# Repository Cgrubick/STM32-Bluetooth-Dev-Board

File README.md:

# STM32-Bluetooth-Dev-Board
STM32 based PCB design
By Clayton Grubick

Overview

This repository contains the design files, firmware, and documentation for a custom-designed PCB featuring an STM32 microcontroller with Bluetooth capabilities. The project is aimed at demonstrating advanced PCB design techniques, including RF circuitry for Bluetooth communication, making it suitable for a wide range of wireless applications.

Features:

  -STM32WB55CEU6 : Utilizes a high-performance STM32 MCU, offering ample processing power for complex applications

  -USB-C Connectivity: Utlizied USB-C with USB2.0 for connecting to the board and communication and power supply. Paired with the USB ESD protection IC

  -LDO Regulator: 5V to 3.3V supply

  -SWD Intereface: SWD connection for programming and debugging

  -RF Circuit: Impedence matching network and a LPF directed into a coaxial connection

  -Bootloader Button: Debouncing circuit and bootloader switch for firmware

  -UART Header Connection

This was my first higher level PCB design and also my first try at designing RF circuits, while the RF portion in this board is pretty trivial it was still a great exercise.

The low pass filter footprint is custom and the 3D model is also included under the 3D models folder, more info and data sheets are also included.

Schematic

PCB

3D view

TODO:

  -Manafuacture PCB
  
  -Write and load firmware onto board
  
  -Perform some simple embedded project with the board such as communication over bluetooth and sending and recieving data from an external computer

Credit/Inspo: Phils Lab

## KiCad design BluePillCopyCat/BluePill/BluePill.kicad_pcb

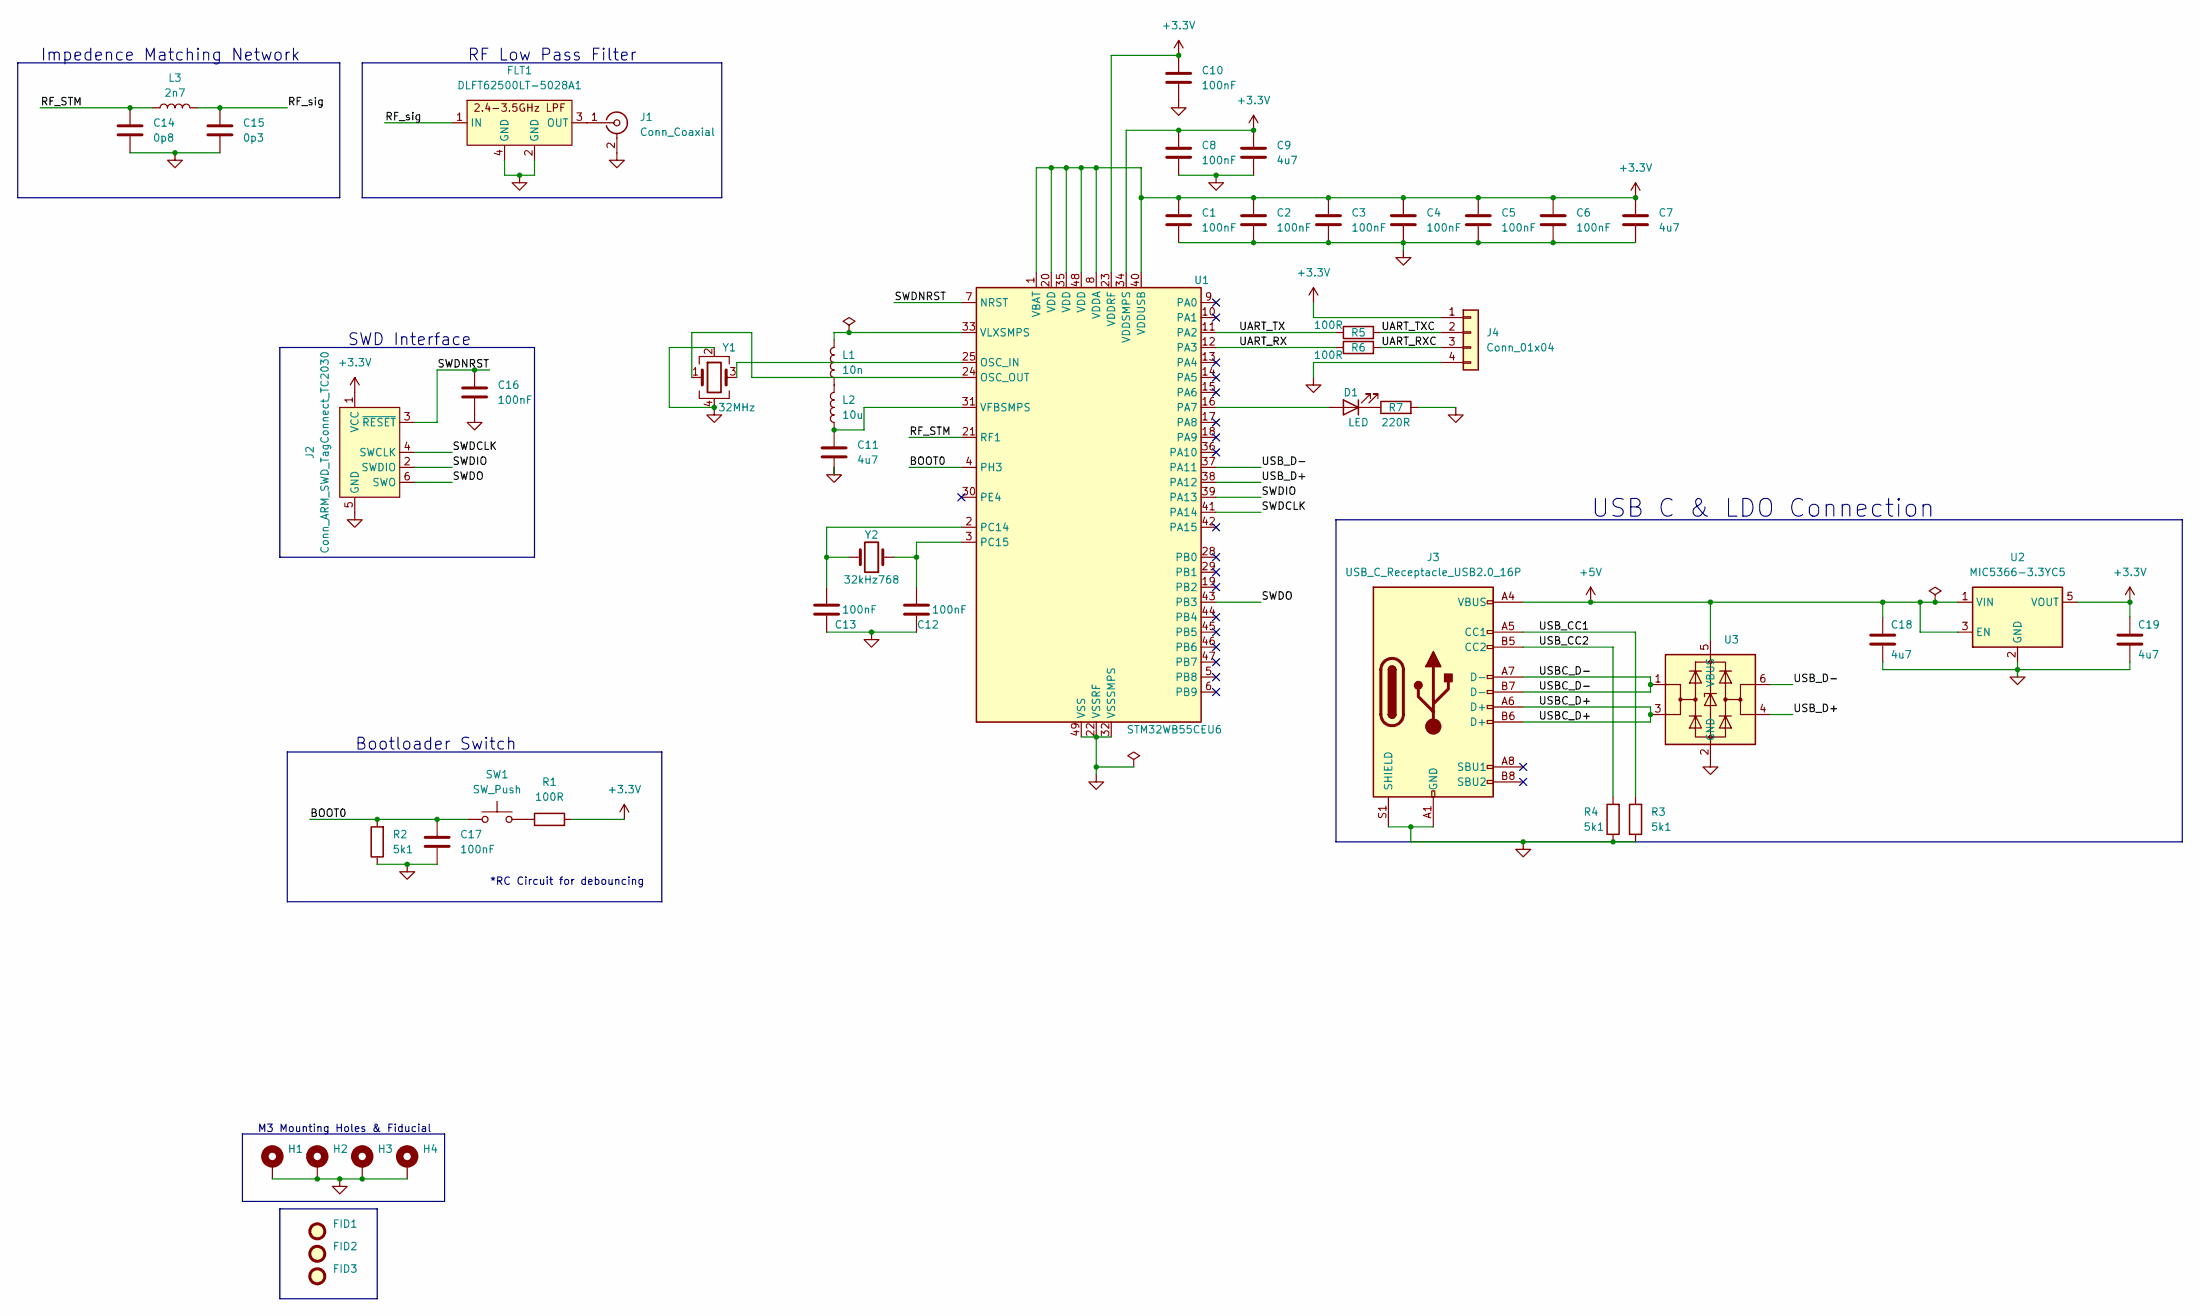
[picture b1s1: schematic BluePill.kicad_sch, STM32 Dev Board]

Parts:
C1, C2, C3, C4, C5, C6, C8, C10, C12, C13, C16, C17: 100nF; C_0402_1005Metric
C7, C9, C11, C18, C19: 4u7; C_0603_1608Metric
C14: 0p8; C_0402_1005Metric
C15: 0p3; C_0402_1005Metric
D1: LED; LED_0402_1005Metric
FID1, FID2, FID3: Fiducial; Fiducial_1mm_Mask2mm
FLT1: DLFT62500LT-5028A1
H1, H2, H3, H4: MountingHole_Pad; MountingHole_2.2mm_M2_Pad_Via
J1: Conn_Coaxial; U.FL_Hirose_U.FL-R-SMT-1_Vertical
J2: Conn_ARM_SWD_TagConnect_TC2030; Tag-Connect_TC2030-IDC-FP_2x03_P1.27mm_Vertical
J3: USB_C_Receptacle_USB2.0_16P; USB_C_Receptacle_GCT_USB4105-xx-A_16P_TopMnt_Horizontal
J4: Conn_01x04; PinSocket_1x04_P2.54mm_Vertical
L1: 10n; L_0402_1005Metric
L2: 10u; L_0805_2012Metric
L3: 2n7; L_0402_1005Metric
R1, R5, R6: 100R; R_0402_1005Metric
R2, R3, R4: 5k1; R_0402_1005Metric
R7: 220R; R_0402_1005Metric
SW1: SW_Push; SW_SPST_CK_RS282G05A3
U1: STM32WB55CEU6; QFN-48-1EP_7x7mm_P0.5mm_EP5.6x5.6mm
U2: MIC5366-3.3YC5; SOT-23-5
U3: SOT-23-6
Y1: 32MHz; Crystal_SMD_2016-4Pin_2.0x1.6mm
Y2: 32kHz768; Crystal_SMD_2012-2Pin_2.0x1.2mm

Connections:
+3.3V: C1.1, C2.1, C3.1, C4.1, C5.1, C6.1, C7.1, C8.1, C9.1, C10.1, C19.1, J2.1 (VCC), J4.1, R1.2, U1.1 (VBAT), U1.8 (VDDA), U1.20 (VDD), U1.23 (VDDRF), U1.34 (VDDSMPS), U1.35 (VDD), U1.40 (VDDUSB), U1.48 (VDD), U2.5 (VOUT)
+5V: C18.1, J3.A4 (VBUS), J3.A9 (VBUS), J3.B4 (VBUS), J3.B9 (VBUS), U2.1 (VIN), U2.3 (EN), U3.5 (VBUS)
/BOOT0: C17.1, R2.2, SW1.1, U1.4 (PH3)
/RF_STM: C14.1, L3.1, U1.21 (RF1)
/RF_sig: C15.1, FLT1.1 (IN), L3.2
/SWDCLK: J2.4 (SWCLK), U1.41 (PA14)
/SWDIO: J2.2 (SWDIO), U1.39 (PA13)
/SWDNRST: C16.1, J2.3 (~RESET), U1.7 (NRST)
/SWDO: J2.6 (SWO), U1.43 (PB3)
/UART_RX: R6.1, U1.12 (PA3)
/UART_RXC: J4.3, R6.2
/UART_TX: R5.1, U1.11 (PA2)
/UART_TXC: J4.2, R5.2
/USBC_D+: J3.A6 (D+), J3.B6 (D+), U3.3
/USBC_D-: J3.A7 (D-), J3.B7 (D-), U3.1
/USB_CC1: J3.A5 (CC1), R3.2
/USB_CC2: J3.B5 (CC2), R4.2
/USB_D+: U1.38 (PA12), U3.4
/USB_D-: U1.37 (PA11), U3.6
GND: C1.2, C2.2, C3.2, C4.2, C5.2, C6.2, C7.2, C8.2, C9.2, C10.2, C11.2, C12.1, C13.1, C14.2, C15.2, C16.2, C17.2, C18.2, C19.2, FLT1.2 (GND), FLT1.4 (GND), H1.1, H2.1, H3.1, H4.1, J1.2 (Ext), J2.5 (GND), J3.A1 (GND), J3.A12 (GND), J3.B1 (GND), J3.B12 (GND), J3.S1 (SHIELD), J4.4, R2.1, R3.1, R4.1, R7.2, U1.22 (VSSRF), U1.32 (VSSSMPS), U1.49 (VSS), U2.2 (GND), U3.2 (GND), Y1.2, Y1.4
unnamed: D1.2 (A), U1.16 (PA7)
unnamed: D1.1 (K), R7.1
unnamed: FLT1.3 (OUT), J1.1 (In)
unnamed: L1.1, L2.2
unnamed: R1.1, SW1.2
unnamed: U1.25 (OSC_IN), Y1.3
unnamed: U1.24 (OSC_OUT), Y1.1
unnamed: C13.2, U1.2 (PC14), Y2.2
unnamed: C12.2, U1.3 (PC15), Y2.1
unnamed: C11.1, L2.1, U1.31 (VFBSMPS)
unnamed: L1.2, U1.33 (VLXSMPS)

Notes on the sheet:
SWD Interface
M3 Mounting Holes & Fiducial
*RC Circuit for debouncing
RF Low Pass Filter
USB C & LDO Connection
Bootloader Switch
Impedence Matching Network

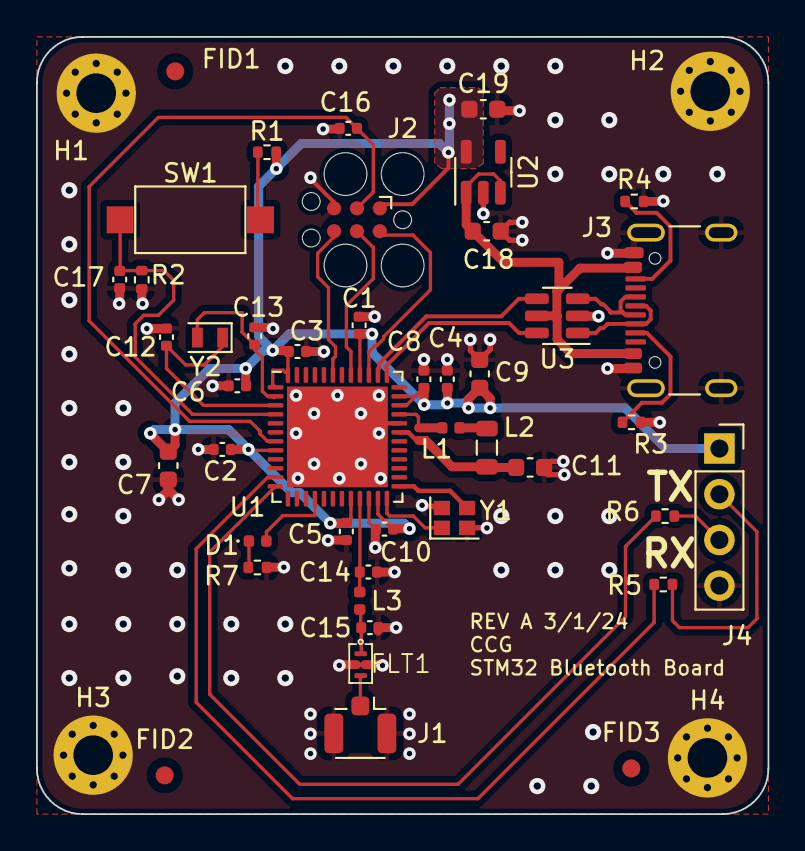
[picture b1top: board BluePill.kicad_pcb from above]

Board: 4 copper layers, 40.6 x 43.2 mm, 48 parts (0 on the bottom side), 31 nets.
